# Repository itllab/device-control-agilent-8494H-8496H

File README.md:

## Device control Agilent 8494H & 8496H
Control of attenuators Agilent/Keysight 8494H &amp; 8496H

Habr: https://habr.com/ru/articles/812755/

+ Scheme:

+ Decoder logic:

+ Cable soldering:

+ It is possible to implement control through the virtual COM port:

+ Appearance:

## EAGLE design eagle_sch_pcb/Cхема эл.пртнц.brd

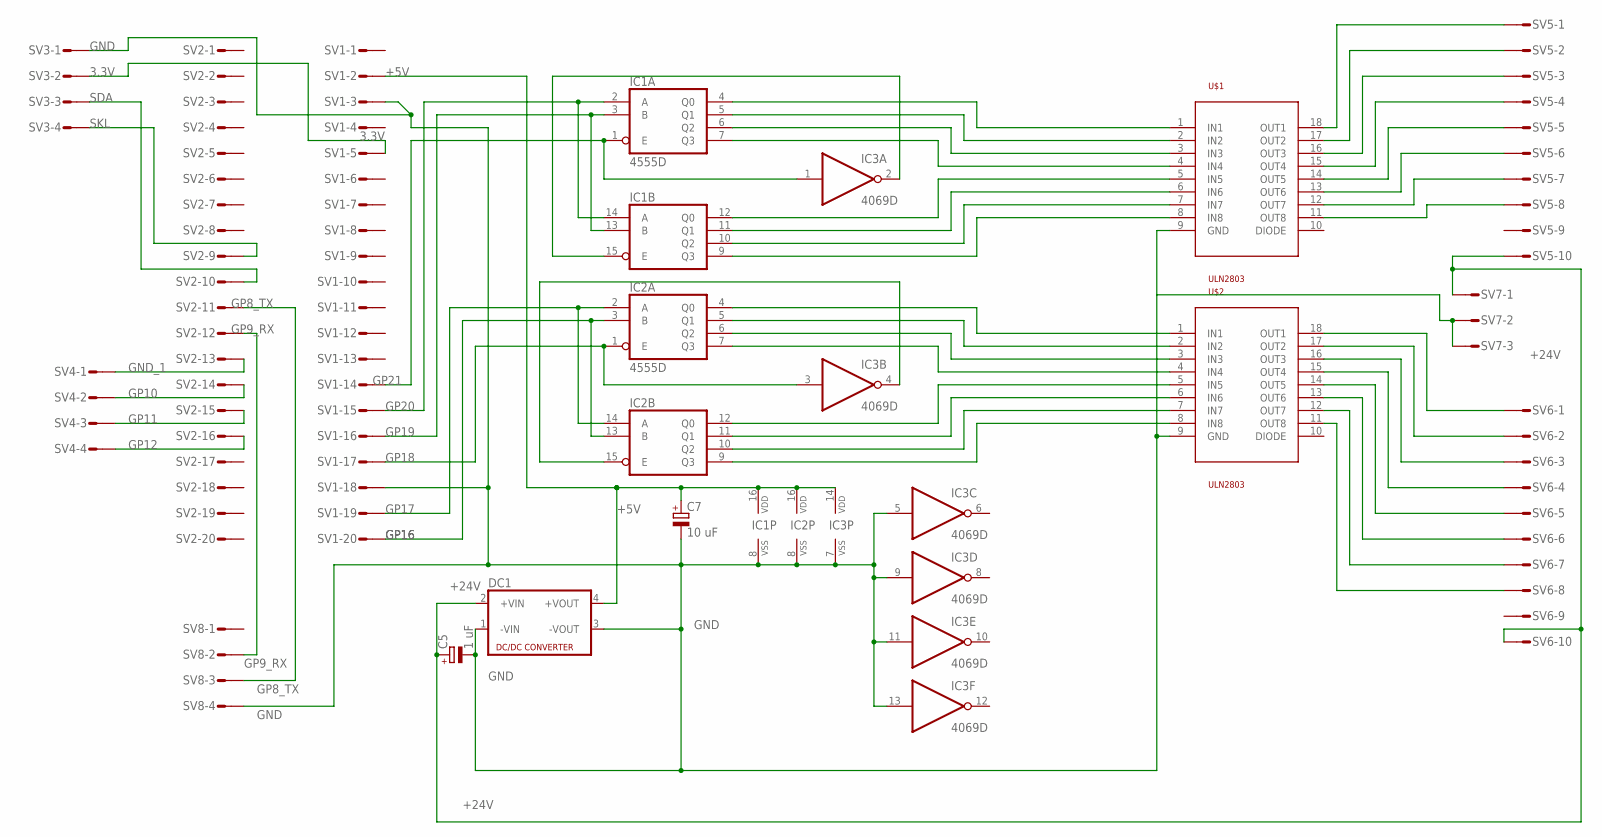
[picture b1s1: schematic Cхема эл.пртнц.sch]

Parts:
C5: 1 uF; SMC_B
C7: 10 uF; SMC_B
DC1: NME
IC1, IC2: 4555D; SO16
IC3: 4069D; SO14
SV1, SV2: S20P
SV3, SV4, SV8: S04P
SV5, SV6: L10P
SV7: L03P
U$1, U$2: ULN2803; SO18L

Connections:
3.3V: SV1.5, SV3.2
+5V: C7.+, DC1.4 (+VOUT), IC1.16 (VDD), IC2.16 (VDD), IC3.14 (VDD), SV1.2
+24V: C5.+, DC1.2 (+VIN), SV5.10, SV6.10, SV7.1
GND: C5.-, C7.-, DC1.1 (-VIN), DC1.3 (-VOUT), IC1.8 (VSS), IC2.8 (VSS), IC3.5 (I), IC3.7 (VSS), IC3.9 (I), IC3.11 (I), IC3.13 (I), SV1.3, SV1.18, SV3.1, SV7.2, SV7.3, SV8.4, U$1.9 (GND), U$2.9 (GND)
GND_1: SV2.13, SV4.1
GP8_TX: SV2.11, SV8.3
GP9_RX: SV2.12, SV8.2
GP10: SV2.14, SV4.2
GP11: SV2.15, SV4.3
GP12: SV2.16, SV4.4
GP16: IC2.3 (B), IC2.13 (B), SV1.20
GP17: IC2.2 (A), IC2.14 (A), SV1.19
GP18: IC2.1 (E), IC3.3 (I), SV1.17
GP19: IC1.3 (B), IC1.13 (B), SV1.16
GP20: IC1.2 (A), IC1.14 (A), SV1.15
GP21: IC1.1 (E), IC3.1 (I), SV1.14
unnamed: IC1.15 (E), IC3.2 (O)
unnamed: IC2.15 (E), IC3.4 (O)
unnamed: IC1.5 (Q1), U$1.2 (IN2)
unnamed: IC1.6 (Q2), U$1.3 (IN3)
unnamed: IC1.7 (Q3), U$1.4 (IN4)
unnamed: IC1.4 (Q0), U$1.1 (IN1)
unnamed: IC1.12 (Q0), U$1.5 (IN5)
unnamed: IC1.11 (Q1), U$1.6 (IN6)
unnamed: IC2.4 (Q0), U$2.1 (IN1)
unnamed: IC2.5 (Q1), U$2.2 (IN2)
unnamed: IC2.6 (Q2), U$2.3 (IN3)
unnamed: IC2.7 (Q3), U$2.4 (IN4)
unnamed: IC1.10 (Q2), U$1.7 (IN7)
unnamed: IC1.9 (Q3), U$1.8 (IN8)
unnamed: SV5.1, U$1.18 (OUT1)
unnamed: SV5.6, U$1.13 (OUT6)
unnamed: SV5.7, U$1.12 (OUT7)
unnamed: SV5.8, U$1.11 (OUT8)
unnamed: SV6.8, U$2.11 (OUT8)
unnamed: SV6.7, U$2.12 (OUT7)
unnamed: SV6.6, U$2.13 (OUT6)
unnamed: SV6.5, U$2.14 (OUT5)
unnamed: SV6.4, U$2.15 (OUT4)
unnamed: SV6.3, U$2.16 (OUT3)
unnamed: SV6.2, U$2.17 (OUT2)
unnamed: SV6.1, U$2.18 (OUT1)
unnamed: IC2.12 (Q0), U$2.5 (IN5)
unnamed: IC2.11 (Q1), U$2.6 (IN6)
unnamed: IC2.10 (Q2), U$2.7 (IN7)
unnamed: IC2.9 (Q3), U$2.8 (IN8)
unnamed: SV5.2, U$1.17 (OUT2)
unnamed: SV5.3, U$1.16 (OUT3)
unnamed: SV5.4, U$1.15 (OUT4)
unnamed: SV5.5, U$1.14 (OUT5)
SDA: SV2.9, SV3.4
SKL: SV2.10, SV3.3

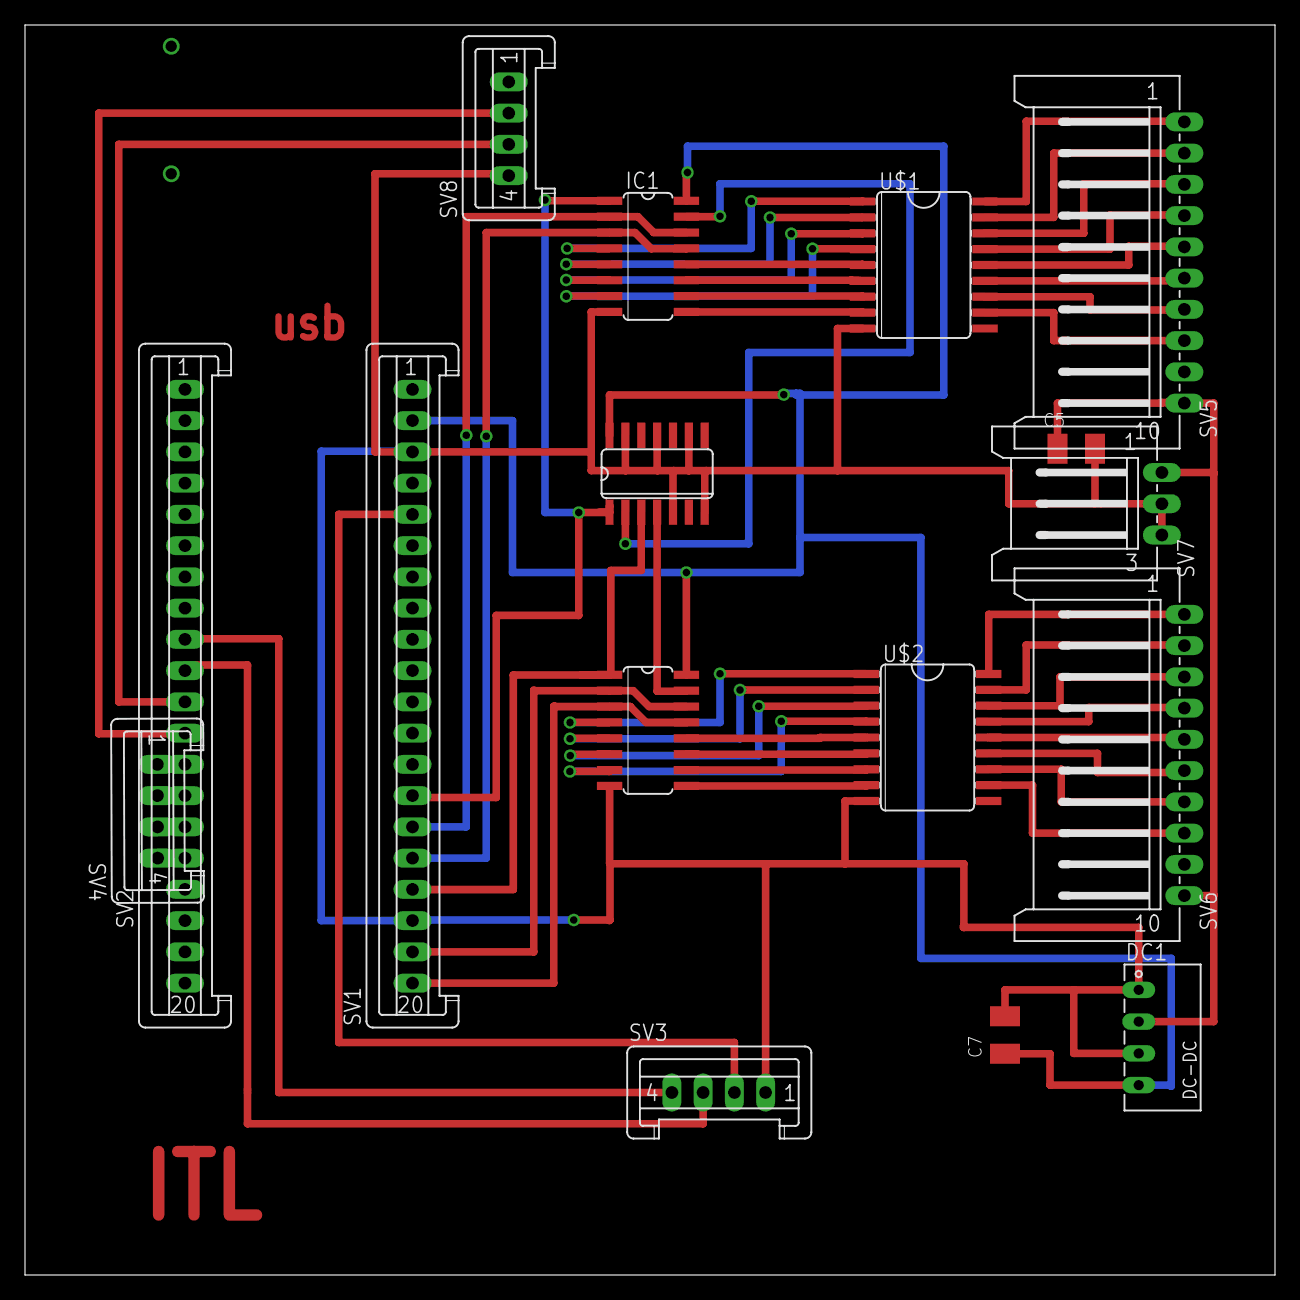
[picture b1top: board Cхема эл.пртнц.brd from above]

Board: 2 copper layers, 100.0 x 100.0 mm, 16 parts (0 on the bottom side), 52 nets.

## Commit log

2022-07-19 Create 1
